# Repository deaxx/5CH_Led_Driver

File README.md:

# 5CH_Led_Driver
5CH Led Driver PT4115 E72-2G4M05S1F/E72-2G4M20S1E

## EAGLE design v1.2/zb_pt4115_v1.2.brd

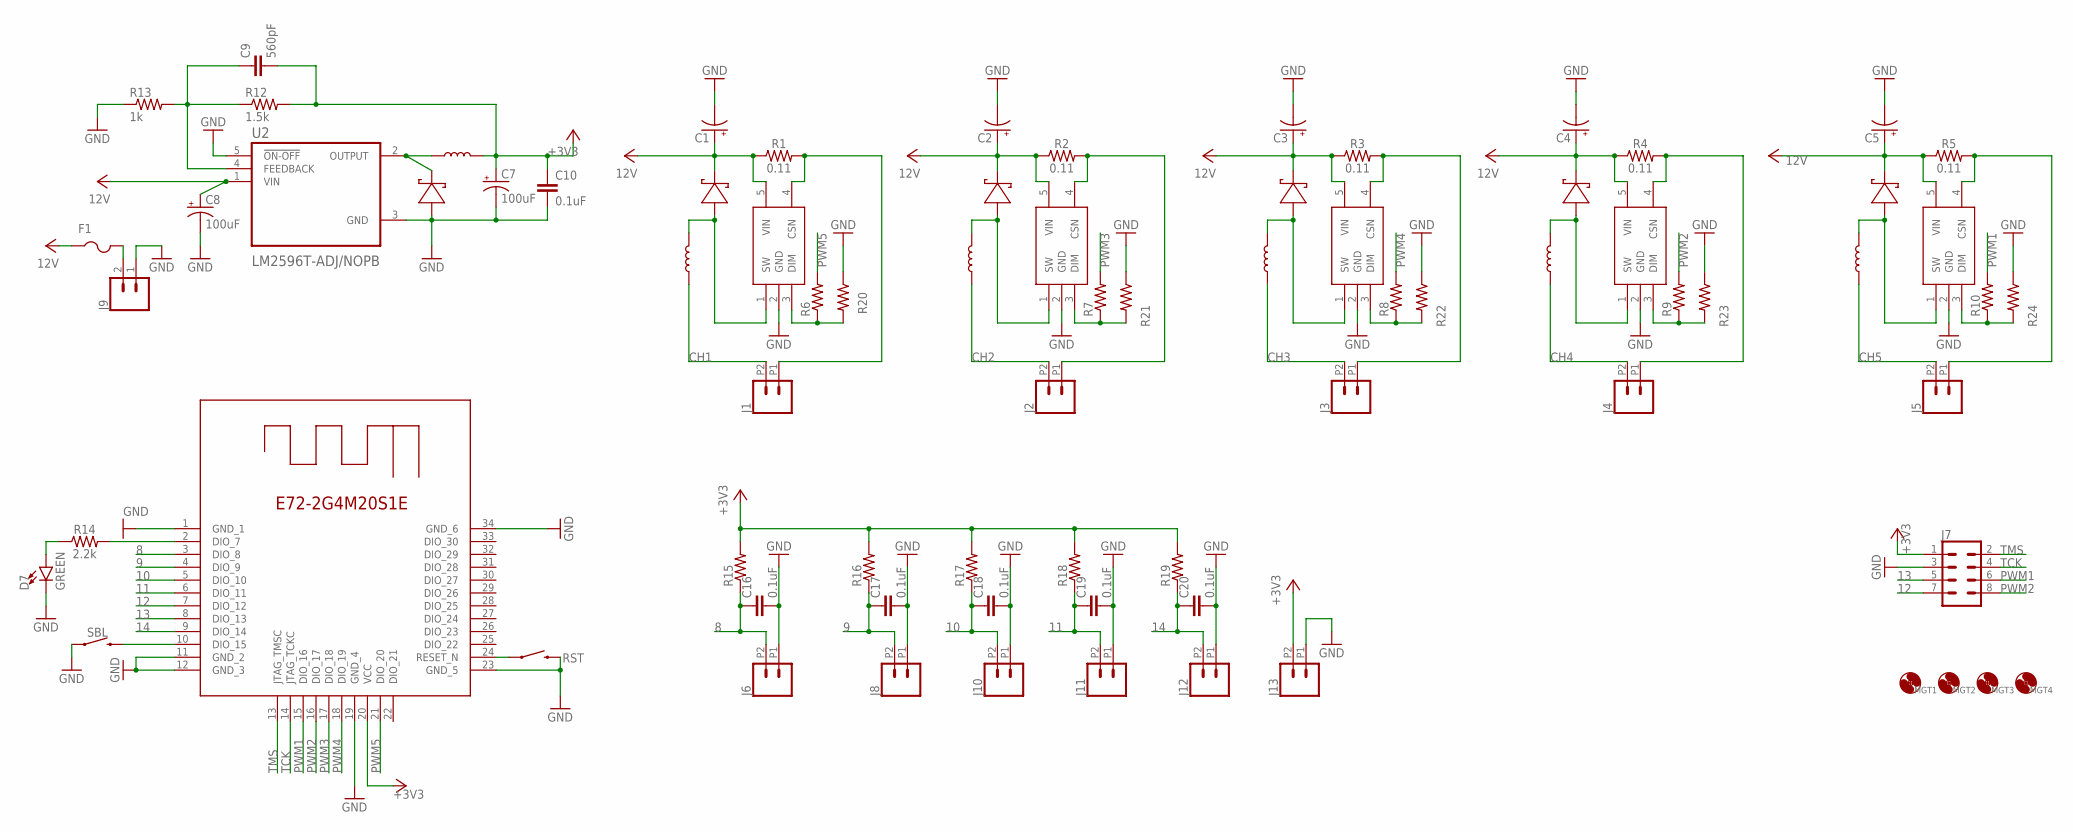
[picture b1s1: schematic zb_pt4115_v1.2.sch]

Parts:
C1, C2, C3, C4, C5: 100uF; EIA7343
C7, C8: 100uF; PANASONIC_D
C9: 560pF; 0603
C10, C16, C17, C18, C19, C20: 0.1uF; 0603
D1, D2, D3, D4, D5, D6: SS18; DIOM5227X270N
D7: GREEN; LED-0603
F1: PTCFUSE-1812; 1812
IC1, IC2, IC3, IC4, IC5, IC6: 68uH; INDPM102100X400N
J1, J2, J3, J4, J5, J6, J8, J10, J11, J12, J13: CONN_022.54MM_SCREWTERM; 1X02_2.54_SCREWTERM
J7: CONN_04X2; 2X4
J9: CONN_025MM; SCREWTERMINAL-5MM-2
MGT1, MGT2, MGT3, MGT4: MOUNT-HOLE3.0; 3,0
R1, R2, R3, R4, R5: 0.11; 2010
R6, R7, R8, R9, R10: 100Ohm; R0805
R12: 1.5k; R0805
R13: 1k; R0805
R14: 2.2k; 0603
R15, R16, R17, R18, R19: 10k; R0805
R20, R21, R22, R23, R24: 3k; R0805
RST: MOMENTARY-SWITCH-SPST-SMD-4.6X2.8MM; TACTILE_SWITCH_SMD_4.6X2.8MM
SBL: MOMENTARY-SWITCH-SPST-SMD-4.6X2.8MM; TACTILE_SWITCH_SMD_4.6X2.8MM
U2: LM2596T-ADJ/NOPB; TO170P1016X470X2092-5
U$1, U$2, U$3, U$4, U$5: PT4115; SOT-89-5
U$6: E72-2G4M20S1E

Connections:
8: C16.1, J6.P2 (2), R15.1, U$6.3 (DIO_8)
9: C17.1, J8.P2 (2), R16.1, U$6.4 (DIO_9)
10: C18.1, J10.P2 (2), R17.1, U$6.5 (DIO_10)
11: C19.1, J11.P2 (2), R18.1, U$6.6 (DIO_11)
12: J7.7, U$6.7 (DIO_12)
13: J7.5, U$6.8 (DIO_13)
14: C20.1, J12.P2 (2), R19.1, U$6.9 (DIO_14)
+3V3: C7.+, C9.2, C10.1, IC6.2, J7.1, J13.P2 (2), R12.2, R15.2, R16.2, R17.2, R18.2, R19.2, U$6.20 (VCC)
CH1: IC1.1, J1.P2 (2)
CH2: IC2.1, J2.P2 (2)
CH3: IC3.1, J3.P2 (2)
CH4: IC4.1, J4.P2 (2)
CH5: IC5.1, J5.P2 (2)
GND: C1.C (-), C2.C (-), C3.C (-), C4.C (-), C5.C (-), C7.-, C8.-, C10.2, C16.2, C17.2, C18.2, C19.2, C20.2, D6.2 (A), D7.C, J6.P1 (1), J7.3, J8.P1 (1), J9.1, J10.P1 (1), J11.P1 (1), J12.P1 (1), J13.P1 (1), R13.1, R20.1, R21.1, R22.1, R23.1, R24.1, RST.3 (2), RST.4 (2), SBL.1, SBL.2 (1), U2.3 (GND), U2.5 (!ON-OFF), U$1.2 (GND), U$2.2 (GND), U$3.2 (GND), U$4.2 (GND), U$5.2 (GND), U$6.1 (GND_1), U$6.11 (GND_2), U$6.12 (GND_3), U$6.19 (GND_4), U$6.23 (GND_5), U$6.34 (GND_6)
unnamed: D1.2 (A), IC1.2, U$1.1 (SW)
unnamed: R6.1, R20.2, U$1.3 (DIM)
unnamed: C9.1, R12.1, R13.2, U2.4 (FEEDBACK)
unnamed: D2.2 (A), IC2.2, U$2.1 (SW)
unnamed: J1.P1 (1), R1.2, U$1.4 (CSN)
unnamed: J2.P1 (1), R2.2, U$2.4 (CSN)
unnamed: R7.1, R21.2, U$2.3 (DIM)
unnamed: R8.1, R22.2, U$3.3 (DIM)
unnamed: D3.2 (A), IC3.2, U$3.1 (SW)
unnamed: J3.P1 (1), R3.2, U$3.4 (CSN)
unnamed: R9.1, R23.2, U$4.3 (DIM)
unnamed: R10.1, R24.2, U$5.3 (DIM)
unnamed: D4.2 (A), IC4.2, U$4.1 (SW)
unnamed: J4.P1 (1), R4.2, U$4.4 (CSN)
unnamed: D7.A, R14.1
unnamed: D6.1 (K), IC6.1, U2.2 (OUTPUT)
unnamed: D5.2 (A), IC5.2, U$5.1 (SW)
unnamed: J5.P1 (1), R5.2, U$5.4 (CSN)
unnamed: RST.1, RST.2 (1), U$6.24 (RESET_N)
unnamed: R14.2, U$6.2 (DIO_7)
unnamed: SBL.3 (2), SBL.4 (2), U$6.10 (DIO_15)
PWM1: J7.6, R10.2, U$6.15 (DIO_16)
PWM2: J7.8, R9.2, U$6.16 (DIO_17)
PWM3: R7.2, U$6.17 (DIO_18)
PWM4: R8.2, U$6.18 (DIO_19)
PWM5: R6.2, U$6.21 (DIO_20)
TCK: J7.4, U$6.14 (JTAG_TCKC)
TMS: J7.2, U$6.13 (JTAG_TMSC)
VCC: C1.A (+), C2.A (+), C3.A (+), C4.A (+), C5.A (+), C8.+, D1.1 (K), D2.1 (K), D3.1 (K), D4.1 (K), D5.1 (K), F1.1, F1.2, J9.2, R1.1, R2.1, R3.1, R4.1, R5.1, U2.1 (VIN), U$1.5 (VIN), U$2.5 (VIN), U$3.5 (VIN), U$4.5 (VIN), U$5.5 (VIN)

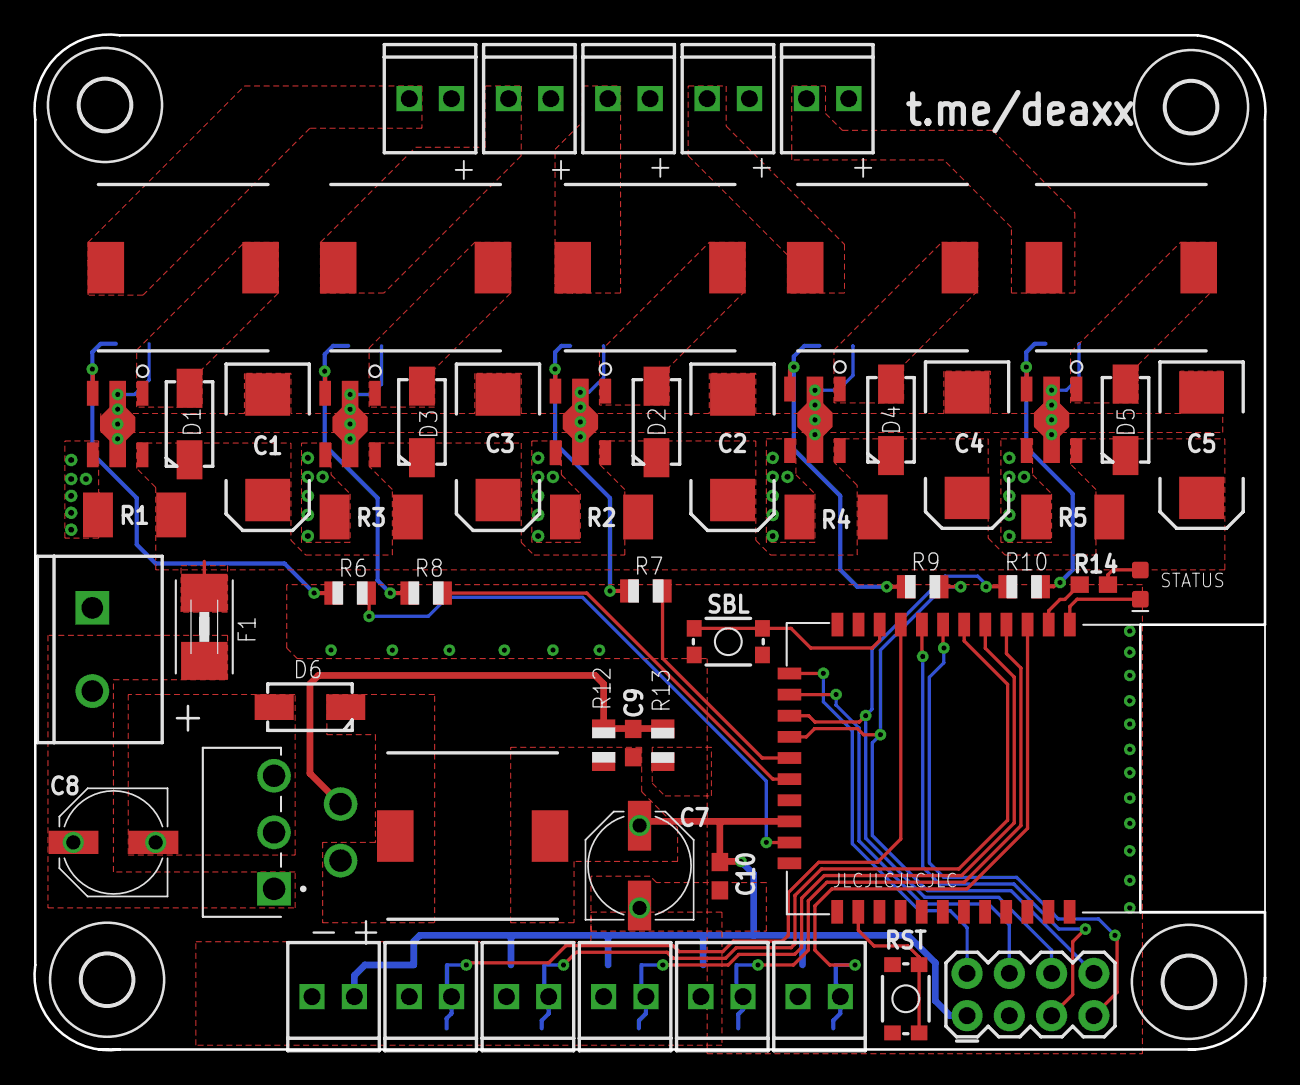
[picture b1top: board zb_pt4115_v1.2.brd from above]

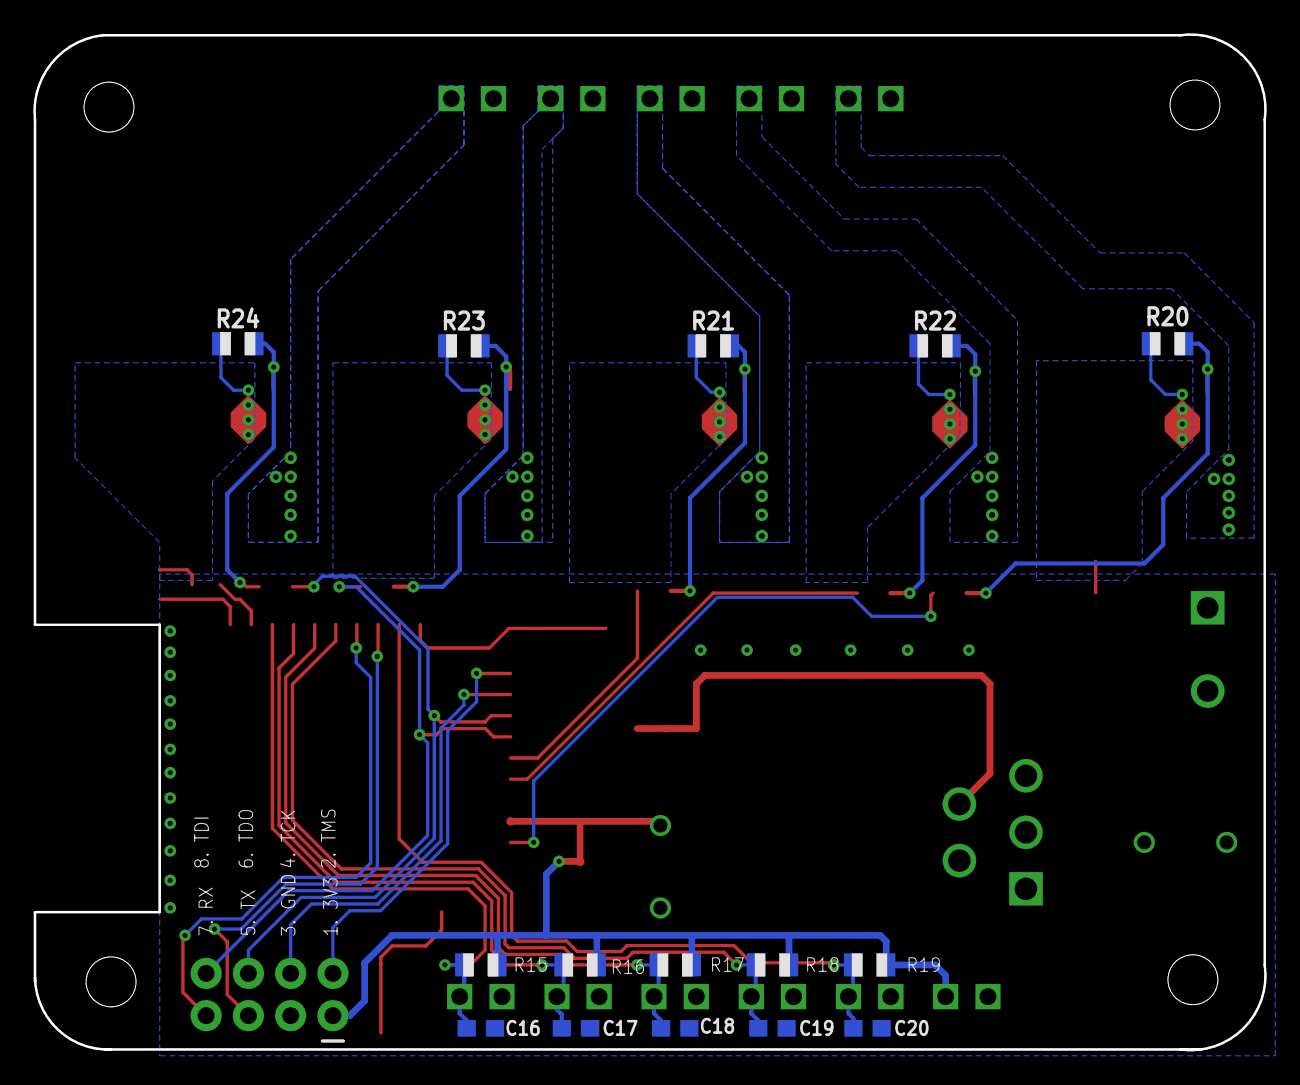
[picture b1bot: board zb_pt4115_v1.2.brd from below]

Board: 2 copper layers, 74.0 x 61.0 mm, 77 parts (15 on the bottom side), 43 nets.

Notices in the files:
parts and their libraries:
SparkFun-Resistors: Licensing: Creative Commons ShareAlike 4.0 International - https://creativecommons.org/licenses/by-sa/4.0
